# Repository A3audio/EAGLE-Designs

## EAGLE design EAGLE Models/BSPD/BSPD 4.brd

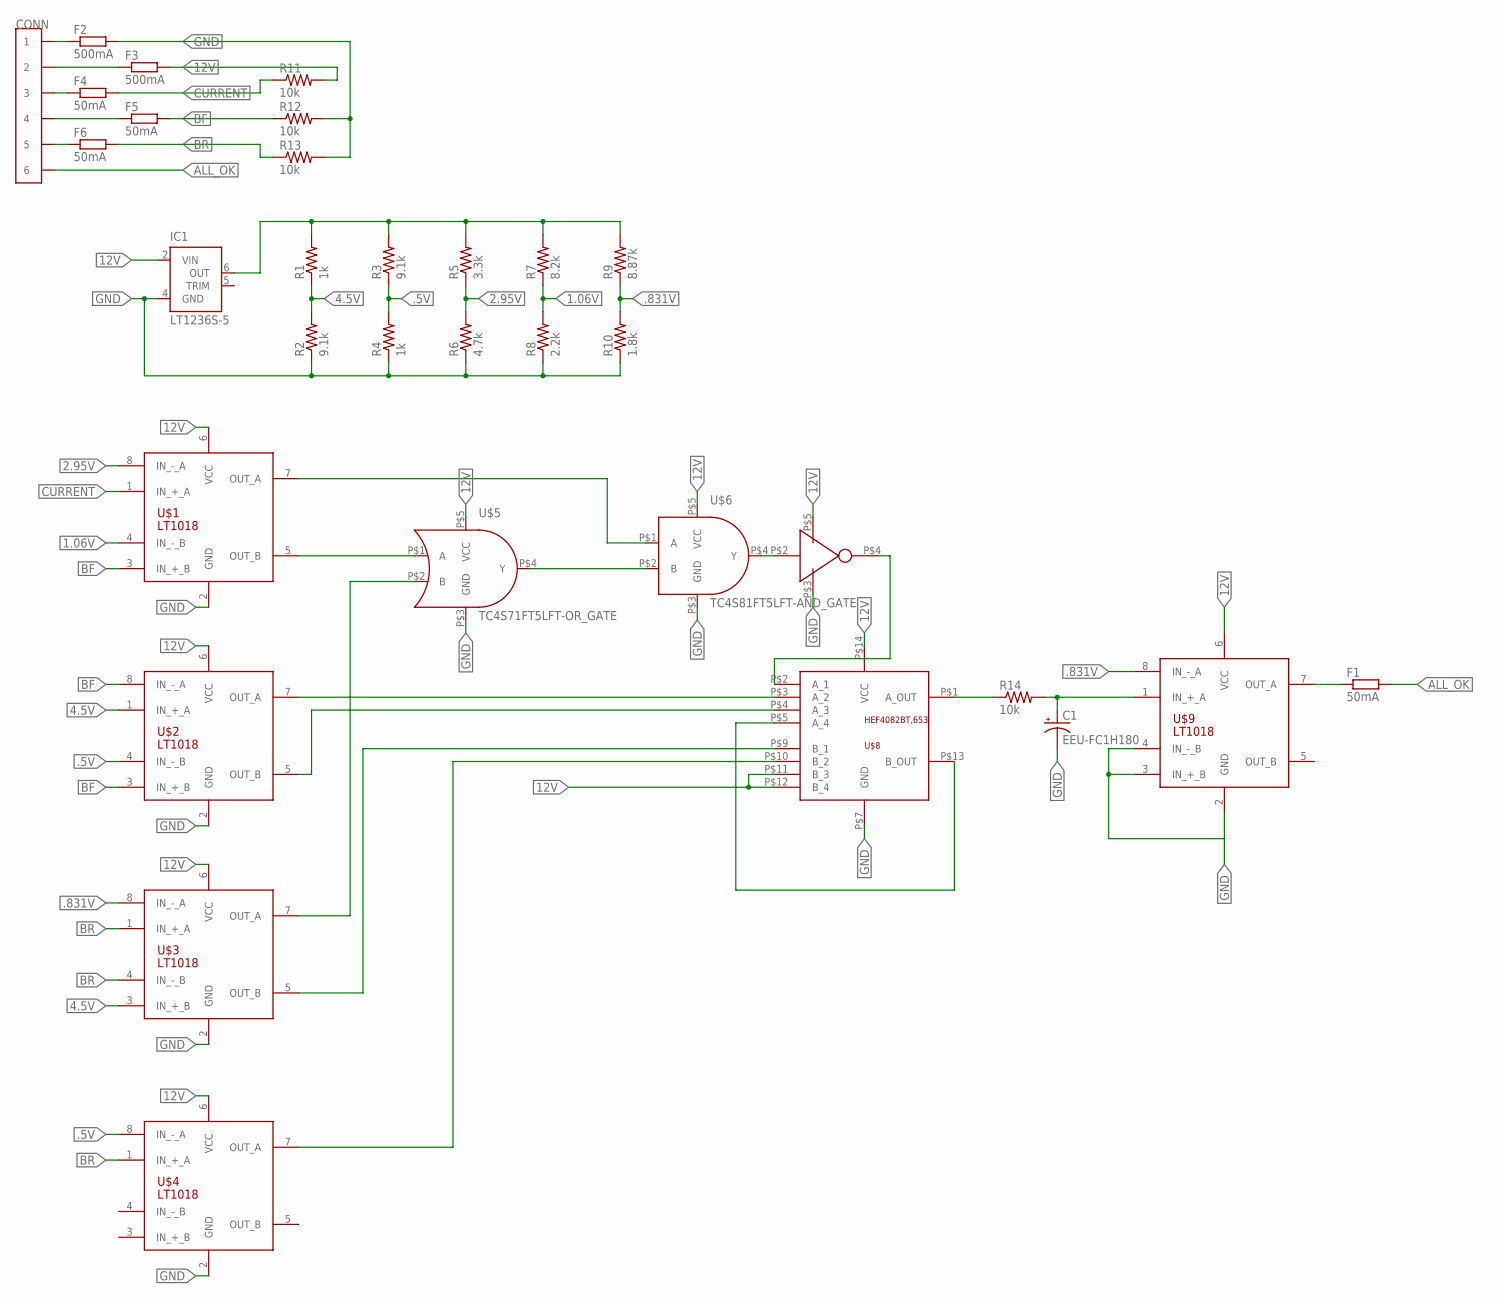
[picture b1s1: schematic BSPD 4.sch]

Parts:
C1: EEU-FC1H180; E2-5
CONN: CONN_6; CONNECTOR_6
F1, F4, F5, F6: 50mA; R0603
F2, F3: 500mA; R0603
IC1: LT1236S-5; SOIC8
R1, R4: 1k; 0603-RES
R2, R3: 9.1k; 0603-RES
R5: 3.3k; 0603-RES
R6: 4.7k; 0603-RES
R7: 8.2k; 0603-RES
R8: 2.2k; 0603-RES
R9: 8.87k; 0603-RES
R10: 1.8k; 0603-RES
R11, R12, R13: 10k; 0603-RES
R14: 10k; R0603
U$1, U$2, U$3, U$4, U$9: LT1018; SOIC8
U$5: TC4S71FT5LFT-OR_GATE; SSOP5-P-0.95
U$6: TC4S81FT5LFT-AND_GATE; SSOP5-P-0.95
U$7: TC4S69F(TE85L,F); SSOP5-P-0.95
U$8: HEF4082BT,653; NXP_14_SOIC

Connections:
1.06V: R7.1, R8.2, U$1.4 (IN_-_B)
2.95V: R5.1, R6.2, U$1.8 (IN_-_A)
4.5V: R1.1, R2.2, U$2.1 (IN_+_A), U$3.3 (IN_+_B)
12V: F3.2, IC1.2 (VIN), R11.2, U$1.6 (VCC), U$2.6 (VCC), U$3.6 (VCC), U$4.6 (VCC), U$5.P$5 (VCC), U$6.P$5 (VCC), U$7.P$5 (VCC), U$8.P$11 (B_3), U$8.P$12 (B_4), U$8.P$14 (VCC), U$9.6 (VCC)
12V_UNFUSED: CONN.3 (2), CONN.4 (2), F3.1
.5V: R3.1, R4.2, U$2.4 (IN_-_B), U$4.8 (IN_-_A)
.831V: R9.1, R10.2, U$3.8 (IN_-_A), U$9.8 (IN_-_A)
ALL_OK: CONN.11 (6), CONN.12 (6), F1.2
BF: F5.2, R12.1, U$1.3 (IN_+_B), U$2.3 (IN_+_B), U$2.8 (IN_-_A)
BF_UNFUSED: CONN.7 (4), CONN.8 (4), F5.1
BR: F6.2, R13.1, U$3.1 (IN_+_A), U$3.4 (IN_-_B), U$4.1 (IN_+_A)
BR_UNFUSED: CONN.9 (5), CONN.10 (5), F6.1
CURRENT: F4.2, R11.1, U$1.1 (IN_+_A)
CURRENT_UNFUSED: CONN.5 (3), CONN.6 (3), F4.1
GND: C1.-, F2.2, IC1.4 (GND), R2.1, R4.1, R6.1, R8.1, R10.1, R12.2, R13.2, U$1.2 (GND), U$2.2 (GND), U$3.2 (GND), U$4.2 (GND), U$5.P$3 (GND), U$6.P$3 (GND), U$7.P$3 (GND), U$8.P$7 (GND), U$9.2 (GND), U$9.3 (IN_+_B), U$9.4 (IN_-_B)
GND_UNFUSED: CONN.1, CONN.2 (1), F2.1
unnamed: IC1.6 (OUT), R1.2, R3.2, R5.2, R7.2, R9.2
unnamed: U$1.5 (OUT_B), U$5.P$1 (A)
unnamed: U$3.7 (OUT_A), U$5.P$2 (B)
unnamed: U$5.P$4 (Y), U$6.P$2 (B)
unnamed: U$1.7 (OUT_A), U$6.P$1 (A)
unnamed: U$6.P$4 (Y), U$7.P$2 (IN)
unnamed: U$7.P$4 (OUT), U$8.P$2 (A_1)
unnamed: U$2.7 (OUT_A), U$8.P$3 (A_2)
unnamed: U$2.5 (OUT_B), U$8.P$4 (A_3)
unnamed: U$8.P$5 (A_4), U$8.P$13 (B_OUT)
unnamed: U$3.5 (OUT_B), U$8.P$9 (B_1)
unnamed: U$4.7 (OUT_A), U$8.P$10 (B_2)
unnamed: R14.1, U$8.P$1 (A_OUT)
unnamed: C1.+, R14.2, U$9.1 (IN_+_A)
unnamed: F1.1, U$9.7 (OUT_A)

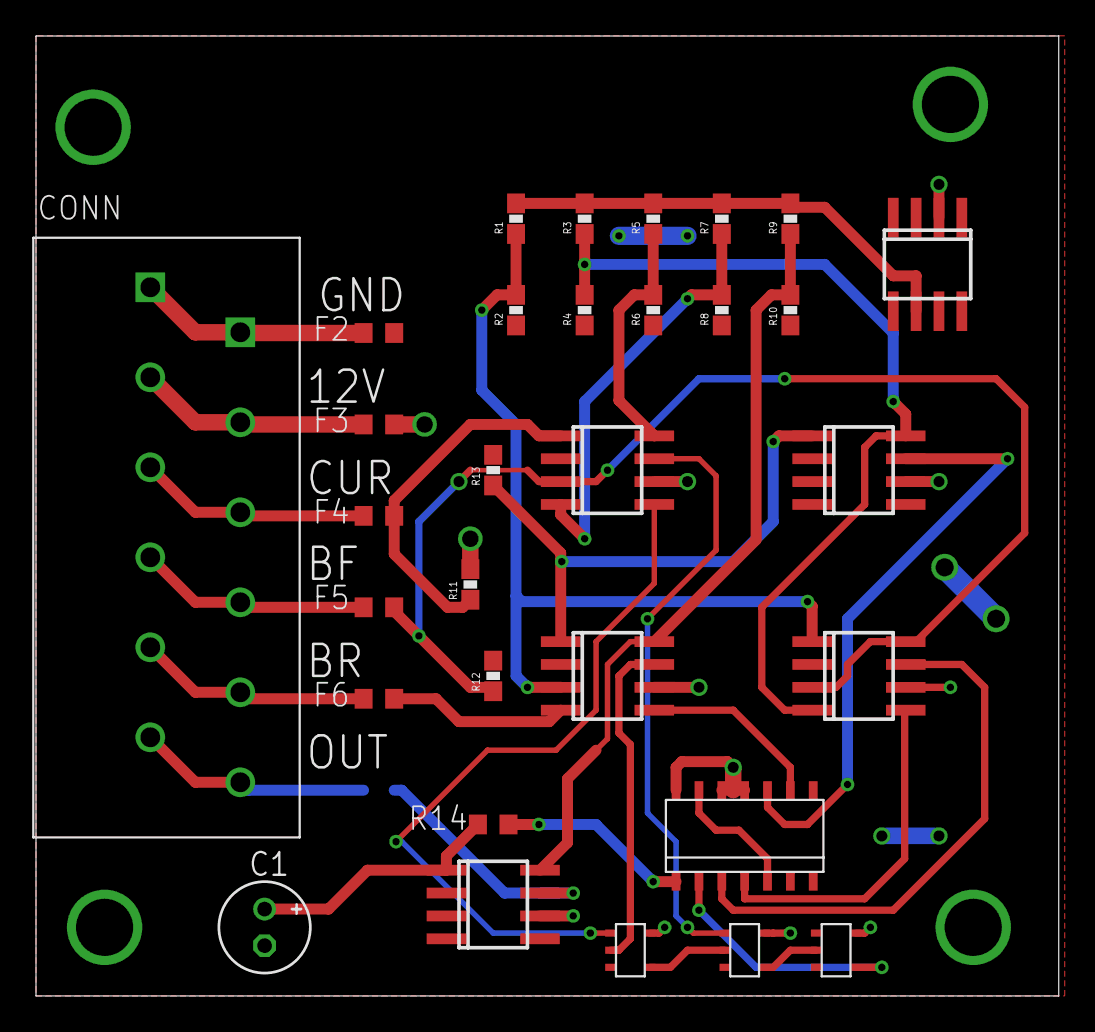
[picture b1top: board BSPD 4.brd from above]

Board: 2 copper layers, 56.8 x 53.3 mm, 32 parts (1 on the bottom side), 31 nets.

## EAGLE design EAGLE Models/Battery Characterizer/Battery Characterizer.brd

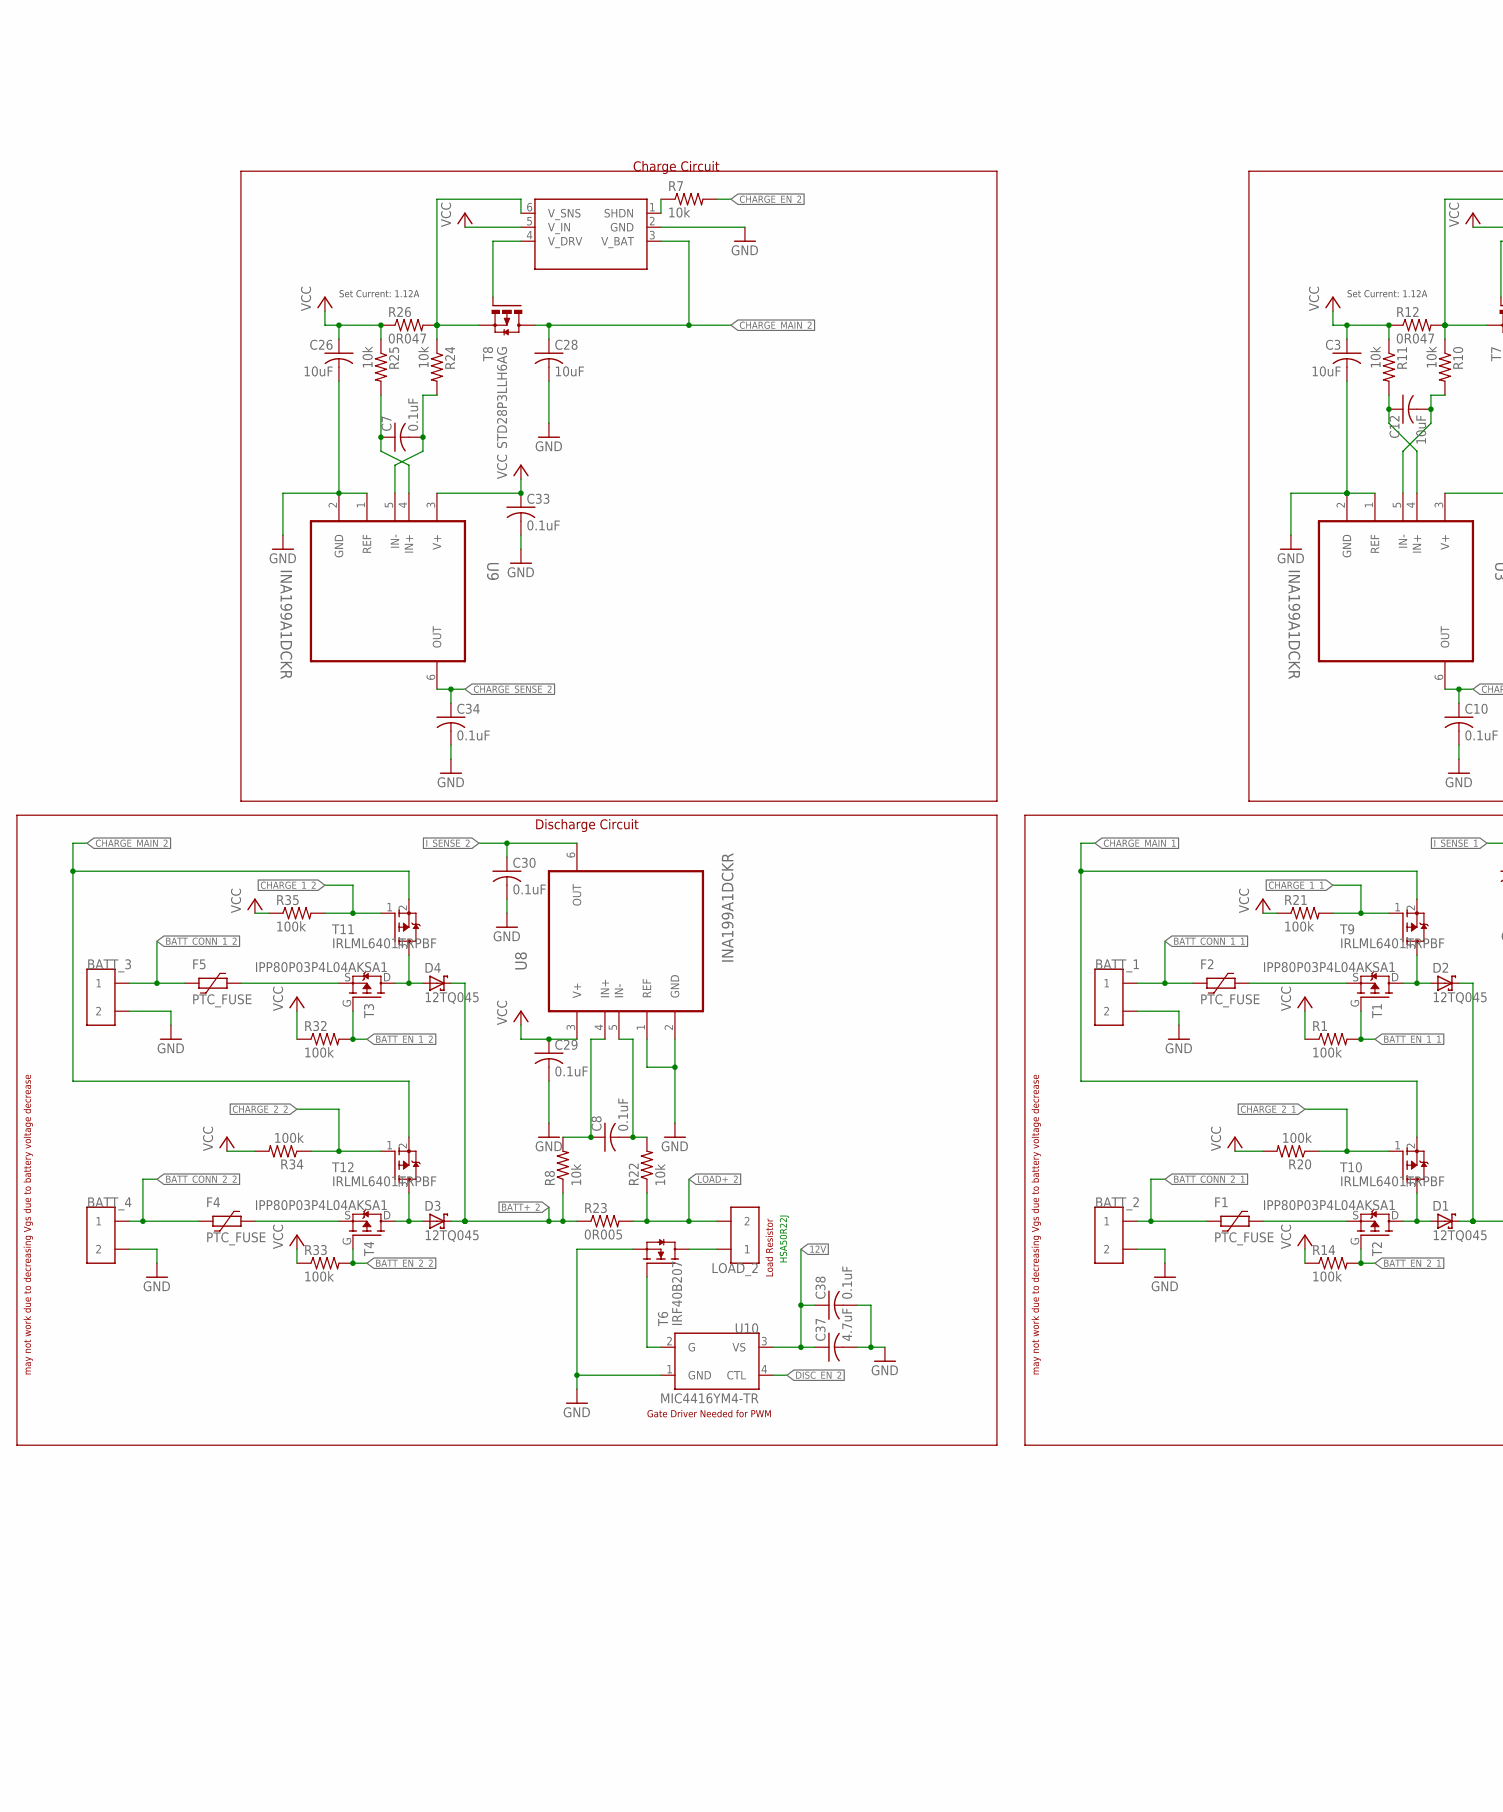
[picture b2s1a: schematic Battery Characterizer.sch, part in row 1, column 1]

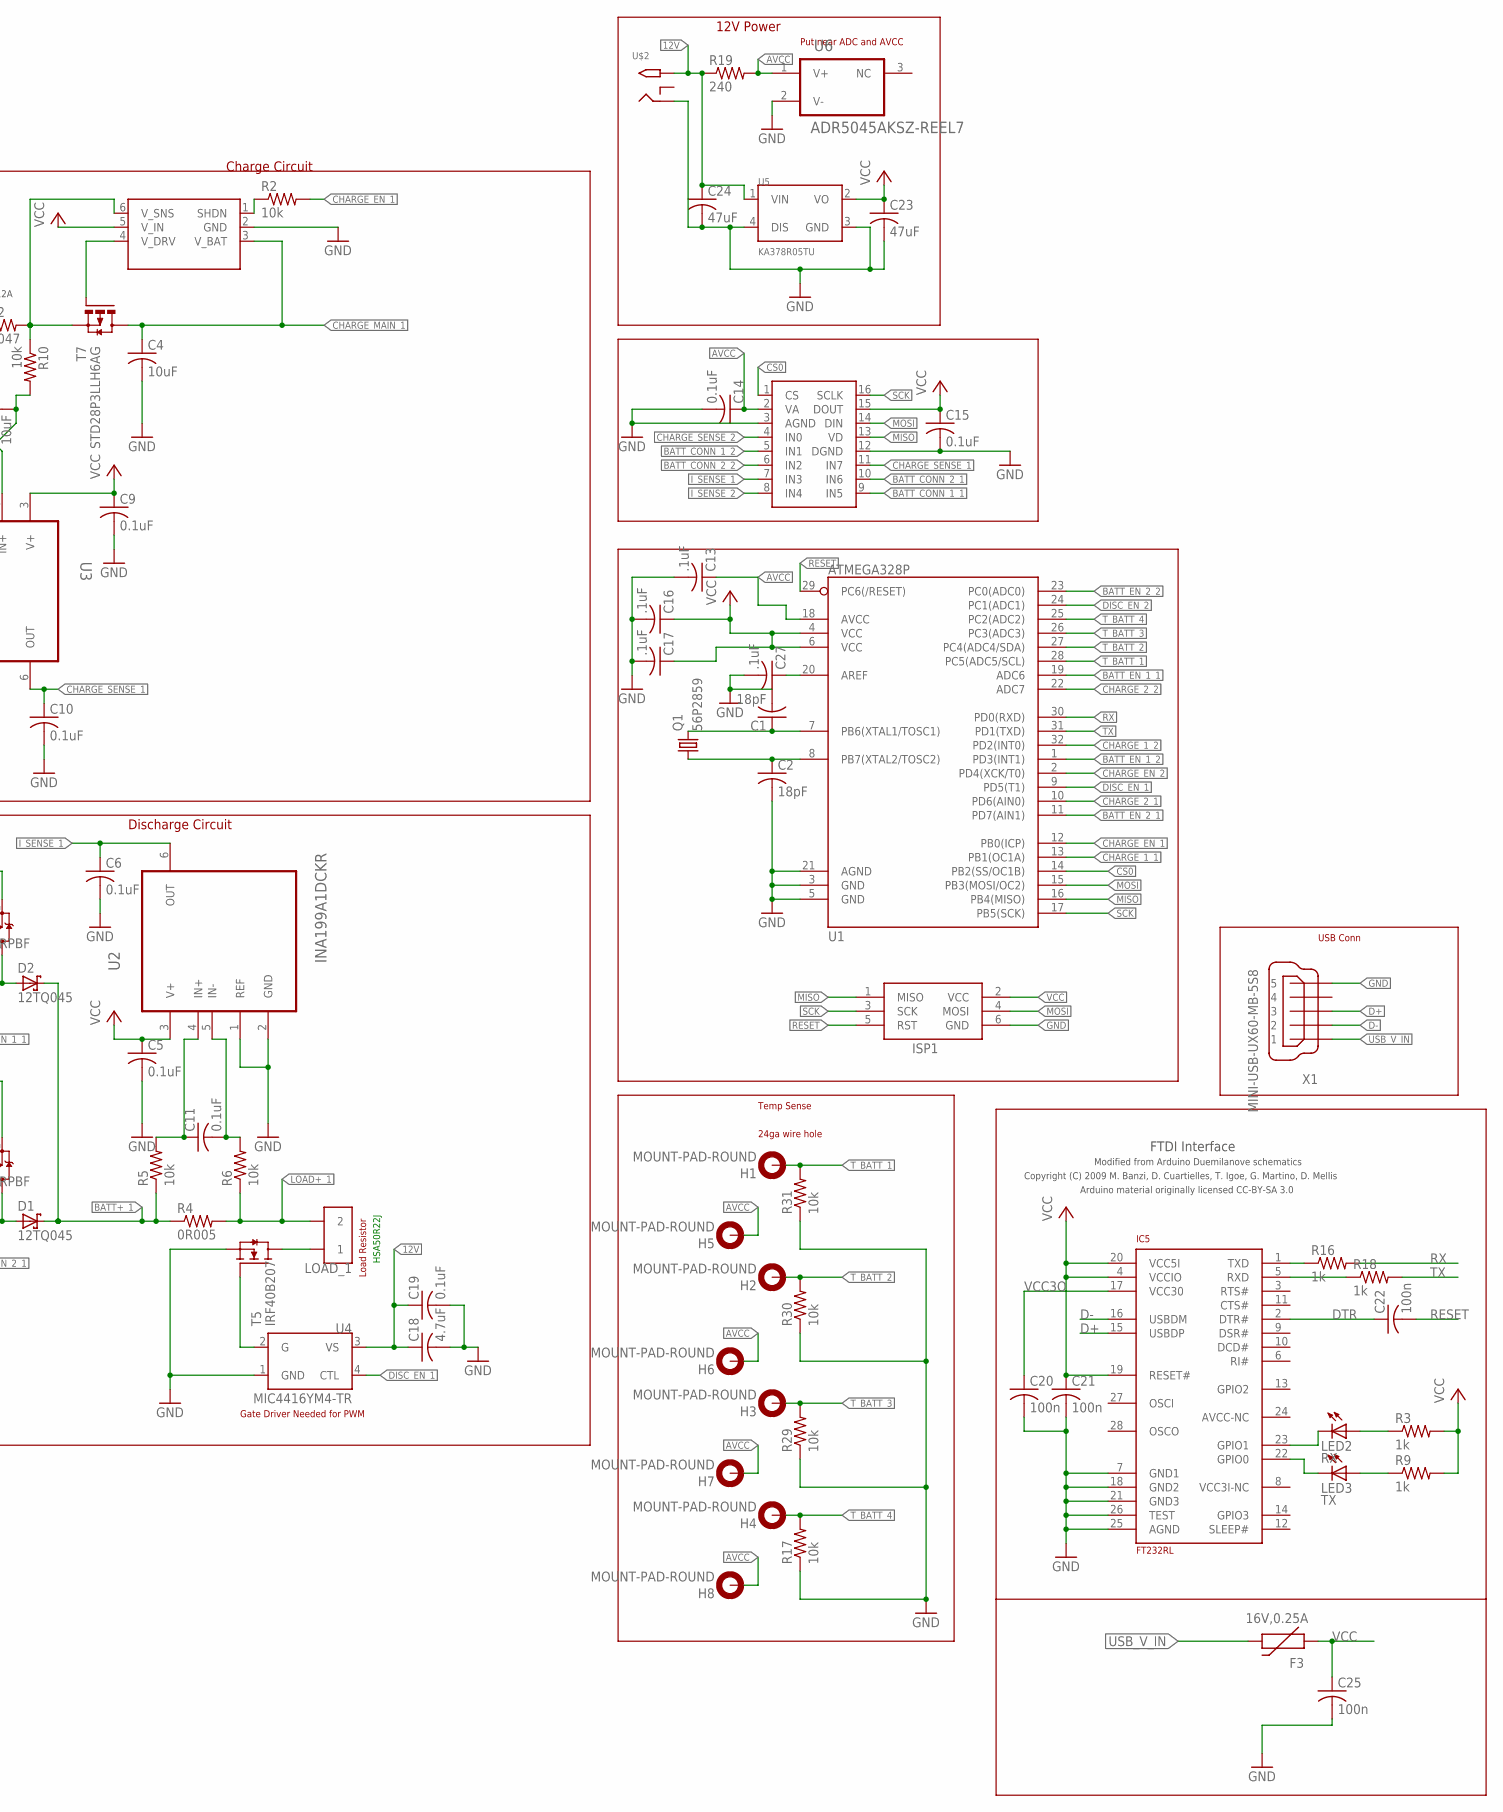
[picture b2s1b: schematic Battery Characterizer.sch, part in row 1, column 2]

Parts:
BATT_1, BATT_2, BATT_3, BATT_4: CONN_2; CONNECTOR_2
C1, C2: 18pF; C0805
C3, C4, C12, C26, C28: 10uF; C0603
C5, C6, C7, C8, C9, C10, C11, C14, C15, C19, C29, C30, C33, C34, C38: 0.1uF; C0603
C13, C16, C17, C27: .1uF; C0603
C18, C37: 4.7uF; C0805
C20, C21, C22, C25: 100n; C0805
C23, C24: 47uF; C0805
D1, D2, D3, D4: 12TQ045; TO220-2
F1, F2, F4, F5: PTC_FUSE; RGEF1100
F3: 16V,0.25A; PTC-1206
H1, H2, H3, H4, H5, H6, H7, H8: MOUNT-PAD-ROUND; 032-PAD
IC5: FT232RL; SSOP28
ISP1: AVRISP-6; AVRISP
LED2: RX; CHIPLED_0805
LED3: TX; CHIPLED_0805
LOAD_1, LOAD_2: CONN_2; CONNECTOR_2
PC1, PC2: MCP73826; SOT23-6
Q1: 56P2859; HC49UP
R1, R14, R20, R21, R32, R33, R34, R35: 100k; M0805
R2, R5, R6, R7, R8, R10, R11, R17, R22, R24, R25, R29, R30, R31: 10k; R0603
R3, R9, R16, R18: 1k; R0805
R4, R23: 0R005; R-3637
R12, R26: 0R047; M1206
R19: 240; R0603
T1, T2, T3, T4: IPP80P03P4L04AKSA1; TO220-3
T5, T6: IRF40B207; TO220-3
T7, T8: STD28P3LLH6AG; D2-PAK
T9, T10, T11, T12: IRLML6401TRPBF; SOT95P237X112-3N
U1: ATMEGA328P; TQFP32-08
U2, U3, U8, U9: INA199A1DCKR; SOT65P210X110-6N
U4, U10: MIC4416YM4-TR; 4-SOT_143
U5: KA378R05TU; TO-220-4
U6: ADR5045AKSZ-REEL7; SOT95P237X112-3N; MPN ADR5045AKSZ-REEL7
U$2: 2.1MMJACKTHM; PJ-102A
U$7: ADC128S022CIMTX/NOPB; TSSOP16
X1: MINI-USB-UX60-MB-5S8; UX60-MB-5S8

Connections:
12V: C18.1, C19.1, C24.1, C37.1, C38.1, R19.1, U4.3 (VS), U5.1 (VIN), U10.3 (VS), U$2.TIP
AREF: C27.1, U1.20 (AREF)
AVCC: C13.1, C14.1, H5.1, H6.1, H7.1, H8.1, R19.2, U1.18 (AVCC), U6.1 (V+), U$7.2 (VA)
BATT+_1: D1.C, D2.C, R4.1, R4.2 (1), R5.1
BATT+_2: D3.C, D4.C, R8.1, R23.1, R23.2 (1)
BATT_CONN_1_1: BATT_1.1, BATT_1.2 (1), F2.P$2 (2), U$7.9 (IN5)
BATT_CONN_1_2: BATT_3.1, BATT_3.2 (1), F5.P$2 (2), U$7.5 (IN1)
BATT_CONN_2_1: BATT_2.1, BATT_2.2 (1), F1.P$2 (2), U$7.10 (IN6)
BATT_CONN_2_2: BATT_4.1, BATT_4.2 (1), F4.P$2 (2), U$7.6 (IN2)
BATT_EN_1_1: R1.2, T1.G, U1.19 (ADC6)
BATT_EN_1_2: R32.2, T3.G, U1.1 (PD3(INT1))
BATT_EN_2_1: R14.2, T2.G, U1.11 (PD7(AIN1))
BATT_EN_2_2: R33.2, T4.G, U1.23 (PC0(ADC0))
CHARGE_1_1: R21.2, T9.1 (G), U1.13 (PB1(OC1A))
CHARGE_1_2: R35.2, T11.1 (G), U1.32 (PD2(INT0))
CHARGE_2_1: R20.1, T10.1 (G), U1.10 (PD6(AIN0))
CHARGE_2_2: R34.1, T12.1 (G), U1.22 (ADC7)
CHARGE_EN_1: R2.2, U1.12 (PB0(ICP))
CHARGE_EN_2: R7.2, U1.2 (PD4(XCK/T0))
CHARGE_MAIN_1: C4.1, PC1.3 (V_BAT), T7.2 (D), T7.P$1 (D), T7.P$2 (D), T7.P$3 (D), T7.P$4 (D), T7.P$5 (D), T7.P$6 (D), T7.P$7 (D), T7.P$8 (D), T7.P$9 (D), T7.P$10 (D), T7.P$11 (D), T7.P$12 (D), T7.P$13 (D), T7.P$14 (D), T7.P$15 (D), T7.P$16 (D), T7.P$17 (D), T7.P$18 (D), T7.P$19 (D), T7.P$20 (D), T7.P$21 (D), T7.P$22 (D), T7.P$23 (D), T7.P$24 (D), T7.P$25 (D), T7.P$26 (D), T7.P$27 (D), T7.P$28 (D), T7.P$29 (D), T7.P$30 (D), T9.2 (S), T10.2 (S)
CHARGE_MAIN_2: C28.1, PC2.3 (V_BAT), T8.2 (D), T8.P$1 (D), T8.P$2 (D), T8.P$3 (D), T8.P$4 (D), T8.P$5 (D), T8.P$6 (D), T8.P$7 (D), T8.P$8 (D), T8.P$9 (D), T8.P$10 (D), T8.P$11 (D), T8.P$12 (D), T8.P$13 (D), T8.P$14 (D), T8.P$15 (D), T8.P$16 (D), T8.P$17 (D), T8.P$18 (D), T8.P$19 (D), T8.P$20 (D), T8.P$21 (D), T8.P$22 (D), T8.P$23 (D), T8.P$24 (D), T8.P$25 (D), T8.P$26 (D), T8.P$27 (D), T8.P$28 (D), T8.P$29 (D), T8.P$30 (D), T11.2 (S), T12.2 (S)
CHARGE_SENSE_1: C10.1, U3.6 (OUT), U$7.11 (IN7)
CHARGE_SENSE_2: C34.1, U9.6 (OUT), U$7.4 (IN0)
CS0: U1.14 (PB2(SS/OC1B)), U$7.1 (CS)
D+: IC5.15 (USBDP), X1.3
D-: IC5.16 (USBDM), X1.2
DISC_EN_1: U1.9 (PD5(T1)), U4.4 (CTL)
DISC_EN_2: U1.24 (PC1(ADC1)), U10.4 (CTL)
DISC_GATE_1: T5.G, U4.2 (G)
DISC_GATE_2: T6.G, U10.2 (G)
DISC_INV_1: C11.2, R6.2, U2.5 (IN-)
DISC_INV_2: C8.2, R22.2, U8.5 (IN-)
DISC_NON_INV_1: C11.1, R5.2, U2.4 (IN+)
DISC_NON_INV_2: C8.1, R8.2, U8.4 (IN+)
DTR: C22.1, IC5.2 (DTR#)
FUSE_OUT_1_1: F2.P$1 (1), T1.S
FUSE_OUT_1_2: F5.P$1 (1), T3.S
FUSE_OUT_2_1: F1.P$1 (1), T2.S
FUSE_OUT_2_2: F4.P$1 (1), T4.S
GATE_1: PC1.4 (V_DRV), T7.1 (G)
GATE_2: PC2.4 (V_DRV), T8.1 (G)
GND: BATT_1.3 (2), BATT_1.4 (2), BATT_2.3 (2), BATT_2.4 (2), BATT_3.3 (2), BATT_3.4 (2), BATT_4.3 (2), BATT_4.4 (2), C1.2, C2.2, C3.2, C4.2, C5.2, C6.2, C9.2, C10.2, C13.2, C14.2, C15.2, C16.2, C17.2, C18.2, C19.2, C20.2, C21.2, C23.2, C24.2, C25.2, C26.2, C27.2, C28.2, C29.2, C30.2, C33.2, C34.2, C37.2, C38.2, IC5.7 (GND1), IC5.18 (GND2), IC5.21 (GND3), IC5.25 (AGND), IC5.26 (TEST), ISP1.6 (GND), PC1.2 (GND), PC2.2 (GND), R17.1, R29.1, R30.1, R31.1, T5.S, T6.S, U1.3 (GND), U1.5 (GND), U1.21 (AGND), U2.1 (REF), U2.2 (GND), U3.1 (REF), U3.2 (GND), U4.1 (GND), U5.3 (GND), U5.4 (DIS), U6.2 (V-), U8.1 (REF), U8.2 (GND), U9.1 (REF), U9.2 (GND), U10.1 (GND), U$2.RING, U$7.3 (AGND), U$7.12 (DGND), X1.5, X1.M1 (5), X1.M2 (5), X1.M3 (5), X1.M4 (5)
INV_1: C12.2, R10.2, U3.5 (IN-)
INV_2: C7.2, R24.2, U9.5 (IN-)
I_SENSE_1: C6.1, U2.6 (OUT), U$7.7 (IN3)
I_SENSE_2: C30.1, U8.6 (OUT), U$7.8 (IN4)
LOAD+_1: LOAD_1.3 (2), LOAD_1.4 (2), R4.3 (2), R4.4 (2), R6.1
LOAD+_2: LOAD_2.3 (2), LOAD_2.4 (2), R22.1, R23.3 (2), R23.4 (2)
M8RXD: IC5.1 (TXD), R16.1
M8TXD: IC5.5 (RXD), R18.1
MISO: ISP1.1 (MISO), U1.16 (PB4(MISO)), U$7.13 (VD)
MOSI: ISP1.4 (MOSI), U1.15 (PB3(MOSI/OC2)), U$7.14 (DIN)
unnamed: IC5.23 (GPIO1), LED2.C
unnamed: IC5.22 (GPIO0), LED3.C
unnamed: LED2.A, R3.1
unnamed: LED3.A, R9.1
NMOS_IN_1: LOAD_1.1, LOAD_1.2 (1), T5.D
NMOS_IN_2: LOAD_2.1, LOAD_2.2 (1), T6.D
NON_INV_1: C12.1, R11.2, U3.4 (IN+)
NON_INV_2: C7.1, R25.2, U9.4 (IN+)
PMOS_OUT_1_1: D2.A, T1.D, T9.3 (D)
PMOS_OUT_1_2: D4.A, T3.D, T11.3 (D)
PMOS_OUT_2_1: D1.A, T2.D, T10.3 (D)
PMOS_OUT_2_2: D3.A, T4.D, T12.3 (D)
RESET: C22.2, ISP1.5 (RST), U1.29 (PC6(/RESET))
RX: R16.2, U1.30 (PD0(RXD))
SCK: ISP1.3 (SCK), U1.17 (PB5(SCK)), U$7.16 (SCLK)
SHDN_1: PC1.1 (SHDN), R2.1
SHDN_2: PC2.1 (SHDN), R7.1
TX: R18.2, U1.31 (PD1(TXD))
T_BATT_1: H1.1, R31.2, U1.28 (PC5(ADC5/SCL))
T_BATT_2: H2.1, R30.2, U1.27 (PC4(ADC4/SDA))
T_BATT_3: H3.1, R29.2, U1.26 (PC3(ADC3))
T_BATT_4: H4.1, R17.2, U1.25 (PC2(ADC2))
USB_V_IN: F3.2, X1.1
VCC: C3.1, C5.1, C9.1, C15.1, C16.1, C17.1, C21.1, C23.1, C25.1, C26.1, C29.1, C33.1, F3.1, IC5.4 (VCCIO), IC5.19 (RESET#), IC5.20 (VCC5I), ISP1.2 (VCC), PC1.5 (V_IN), PC2.5 (V_IN), R1.1, R3.2, R9.2, R11.1, R12.1, R14.1, R20.2, R21.1, R25.1, R26.1, R32.1, R33.1, R34.2, R35.1, U1.4 (VCC), U1.6 (VCC), U2.3 (V+), U3.3 (V+), U5.2 (VO), U8.3 (V+), U9.3 (V+), U$7.15 (DOUT)
VCC3O: C20.1, IC5.17 (VCC30)
V_SNS_1: PC1.6 (V_SNS), R10.1, R12.2, T7.3 (S)
V_SNS_2: PC2.6 (V_SNS), R24.1, R26.2, T8.3 (S)
XTAL1: C1.1, Q1.2, U1.7 (PB6(XTAL1/TOSC1))
XTAL2: C2.1, Q1.1, U1.8 (PB7(XTAL2/TOSC2))

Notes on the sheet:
Set Current: 1.12A
Load Resistor
Gate Driver Needed for PWM
may not work due to decreasing Vgs due to battery voltage decrease
Discharge Circuit
Charge Circuit
Temp Sense
24ga wire hole
12V Power
Put near ADC and AVCC
FTDI Interface
Modified from Arduino Duemilanove schematics
Copyright (C) 2009 M. Banzi, D. Cuartielles, T. Igoe, G. Martino, D. Mellis
Arduino material originally licensed CC-BY-SA 3.0
USB Conn
HSA50R22J

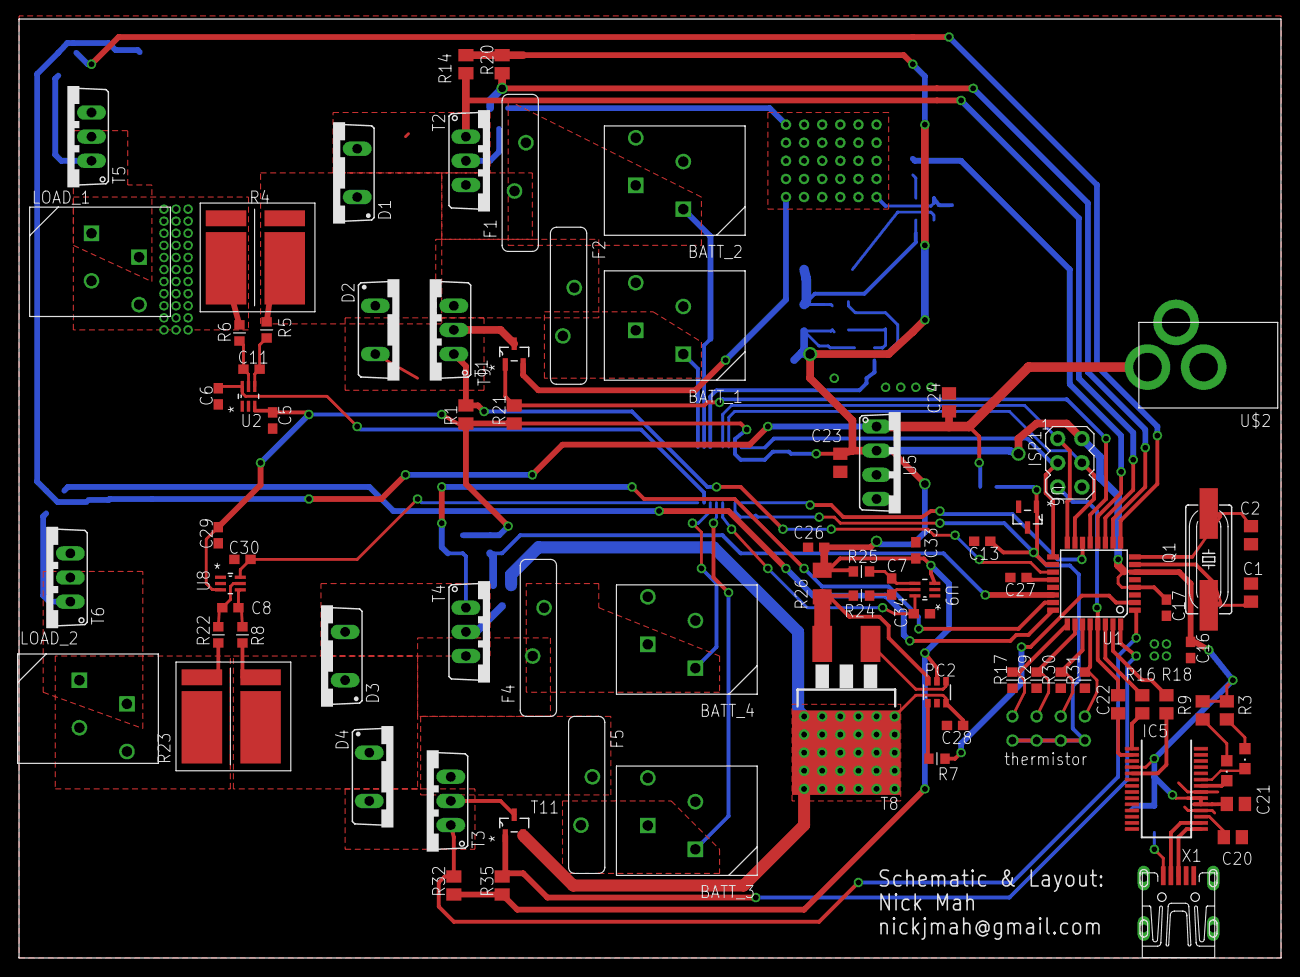
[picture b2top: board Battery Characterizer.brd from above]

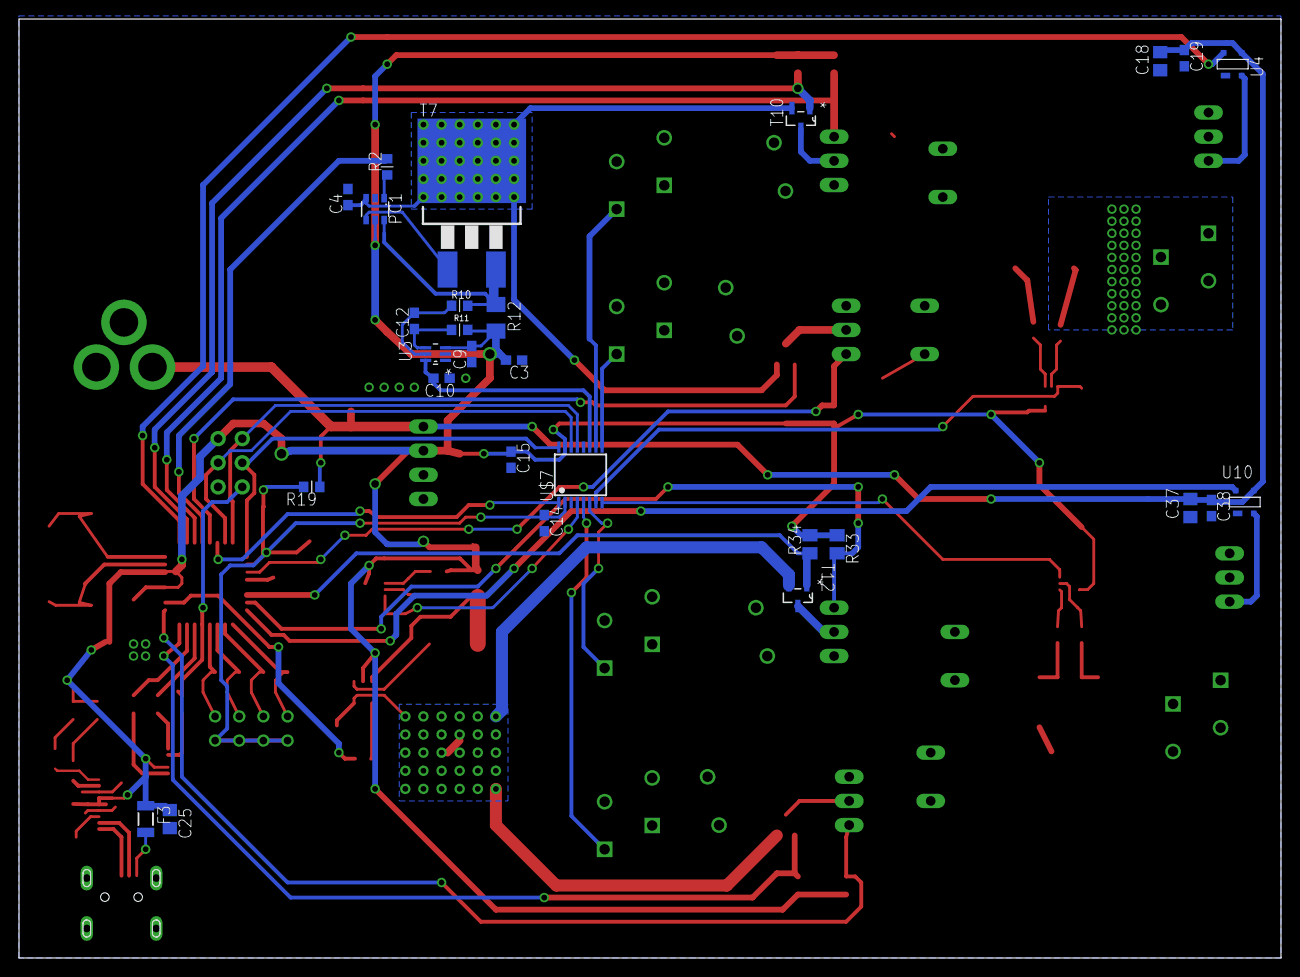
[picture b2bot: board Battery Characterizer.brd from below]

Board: 2 copper layers, 132.7 x 98.7 mm, 119 parts (28 on the bottom side), 81 nets.

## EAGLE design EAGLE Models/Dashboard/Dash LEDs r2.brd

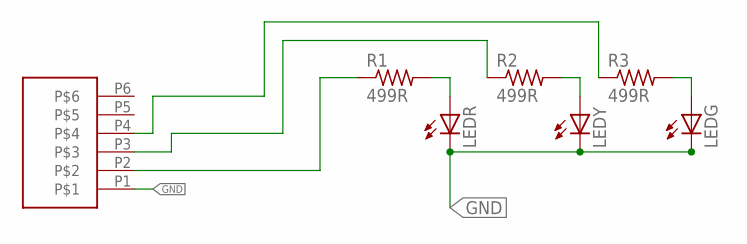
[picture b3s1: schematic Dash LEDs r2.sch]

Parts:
LEDG: LED5MM
LEDR: LED5MM
LEDY: LED5MM
R1, R2, R3: 499R; R0805
U$1: MICRO6LOCK

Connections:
DRV1: R1.1, U$1.P2
DRV2: R2.1, U$1.P3
DRV3: R3.1, U$1.P4
GND: LEDG.K (C), LEDR.K (C), LEDY.K (C), U$1.P1
unnamed: LEDR.A, R1.2
unnamed: LEDY.A, R2.2
unnamed: LEDG.A, R3.2

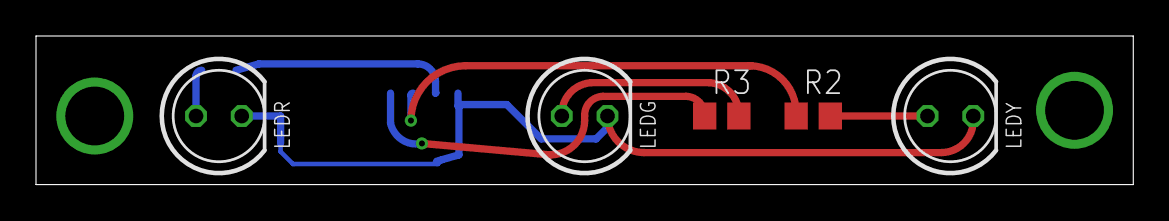
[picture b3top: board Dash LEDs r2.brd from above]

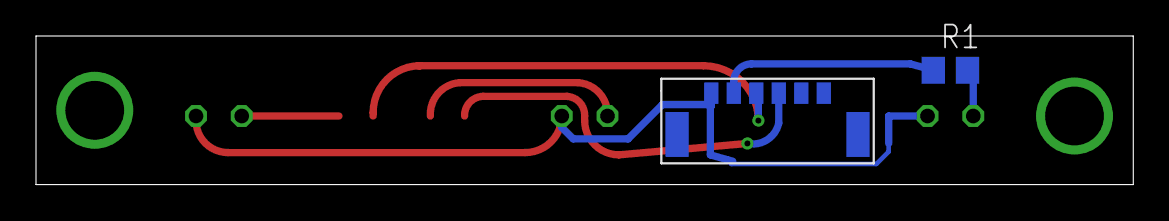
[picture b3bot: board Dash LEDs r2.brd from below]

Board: 2 copper layers, 61.0 x 8.3 mm, 7 parts (2 on the bottom side), 7 nets.

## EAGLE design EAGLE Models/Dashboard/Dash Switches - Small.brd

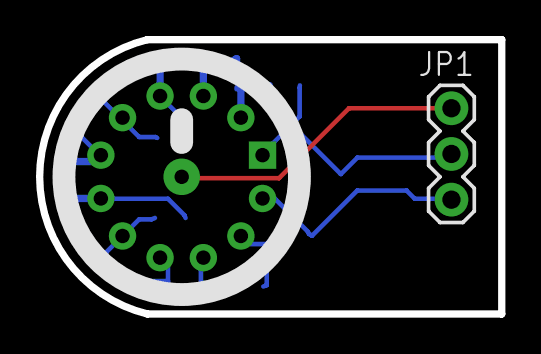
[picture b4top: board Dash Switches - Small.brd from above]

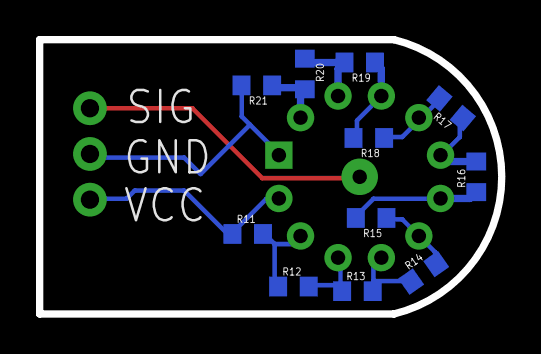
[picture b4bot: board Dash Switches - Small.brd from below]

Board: 2 copper layers, 25.7 x 15.2 mm, 13 parts (11 on the bottom side), 13 nets.

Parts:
JP1: 1X03
R11, R12, R13, R14, R15, R16, R17, R18, R19, R20, R21: 1k; R0603
U$2: ROTSWITCH

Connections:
GND: JP1.2, R21.2, U$2.P$12
unnamed: R11.2, R12.1, U$2.P$2
unnamed: R12.2, R13.1, U$2.P$3
unnamed: R13.2, R14.1, U$2.P$4
unnamed: R14.2, R15.1, U$2.P$5
unnamed: R17.2, R18.1, U$2.P$8
unnamed: R18.2, R19.1, U$2.P$9
unnamed: R15.2, R16.1, U$2.P$6
unnamed: R16.2, R17.1, U$2.P$7
unnamed: R19.2, R20.1, U$2.P$10
unnamed: JP1.1, U$2.P$13
unnamed: R20.2, R21.1, U$2.P$11
VCC: JP1.3, R11.1, U$2.P$1

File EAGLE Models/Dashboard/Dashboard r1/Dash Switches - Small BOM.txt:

Partlist exported from /Users/thomaswillson/Documents/EAGLE/EAGLE Models/Dashboard/Dash Switches - Small.sch at 4/14/16 6:06 PM

Part Value      Device     Package    Description                          
JP1  M02PTH2    M02PTH2    1X02_BIG   Standard 2-pin 0.1" header. Use with 
R11  1k         R-US_R0603 R0603      RESISTOR, American symbol            
R12  1k         R-US_R0603 R0603      RESISTOR, American symbol            
R13  1k         R-US_R0603 R0603      RESISTOR, American symbol            
R14  1k         R-US_R0603 R0603      RESISTOR, American symbol            
R15  1k         R-US_R0603 R0603      RESISTOR, American symbol            
R16  1k         R-US_R0603 R0603      RESISTOR, American symbol            
R17  1k         R-US_R0603 R0603      RESISTOR, American symbol            
R18  1k         R-US_R0603 R0603      RESISTOR, American symbol            
R19  1k         R-US_R0603 R0603      RESISTOR, American symbol            
R20  1k         R-US_R0603 R0603      RESISTOR, American symbol            
R21  1k         R-US_R0603 R0603      RESISTOR, American symbol            
U$2  ROTSWITCH  ROTSWITCH  ROTSWITCH                                       
U$3  MICRO6LOCK MICRO6LOCK MICRO6LOCK

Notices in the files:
parts and their libraries:
SparkFun-Resistors: Licensing: CC v3.0 Share-Alike You are welcome to use this library for commercial purposes.
